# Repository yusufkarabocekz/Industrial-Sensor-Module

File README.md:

# Industrial Sensor Module

## Overview
This industrial sensor module is designed for factory automation applications, providing real-time environmental monitoring of temperature, humidity, and air quality (VOC). The module is built to withstand harsh industrial conditions and supports multiple communication protocols, making it a versatile solution for various automation systems.

## Features
- **Power Input:** 9-24V DC
- **Voltage Regulation:**
  - 5V and 3.3V regulators (LDO and DC-DC buck converter)
- **Sensors:**
  - SHT31 (Temperature & Humidity, I2C)
  - CCS811 (VOC and CO2, I2C)
  - External Analog Input (0-5V, read through 12-bit ADC)
- **Communication Interfaces:**
  - RS485 (Modbus RTU support)
  - UART & I2C external pins
  - ESP32C3 Mini onboard
- **PCB Specifications:**
  - **Dimensions:** 50mm x 50mm
  - **Layer Count:** 4-layer PCB for improved signal integrity and EMI resistance
  - **Terminal Blocks:** Phoenix Contact (or equivalent) screw terminals for RS485 and power input
  - **ESD Protection:** TVS diodes on input lines to ensure robustness

## PCB Design
The PCB layout is optimized to minimize the influence of airflow on sensor measurements. The module is compact, modular, and suitable for various industrial applications.

## PCB Images
### Front View
The front side of the PCB features the ESP32C3 Mini, sensor modules, and necessary components for power regulation and communication. 

### Back View
The back side of the PCB includes additional circuit traces, connectors, and protection components. 

### Angled View
This perspective provides a detailed look at the board's overall design, component placement, and the layout strategy used to optimize performance and durability.

## Getting Started
### Hardware Setup
1. Provide a **9-24V DC** power input via the terminal block.
2. Connect RS485 for Modbus RTU communication or use UART/I2C for direct interfacing.
3. Read sensor values via ESP32C3 Mini or any other microcontroller with supported interfaces.

### Firmware Development
- The ESP32C3 Mini can be programmed using **ESP-IDF** or **Arduino framework**.
- Libraries required:
  - `Wire.h` for I2C communication
  - `ModbusMaster.h` for Modbus RTU communication (if needed)
  - `Adafruit_SHT31.h` for SHT31 sensor
  - `Adafruit_CCS811.h` for CCS811 sensor

## Gerber Files & Manufacturing
- The **Gerber files** are available in the `gerber/` directory.
- Recommended PCB manufacturing specs:
  - **Layer Count:** 4
  - **Copper Thickness:** 1oz
  - **Surface Finish:** ENIG

## Contact
For any inquiries or contributions, feel free to open an issue or reach out.

---
_Designed with KiCad._ Designed by Yusuf Karabocek

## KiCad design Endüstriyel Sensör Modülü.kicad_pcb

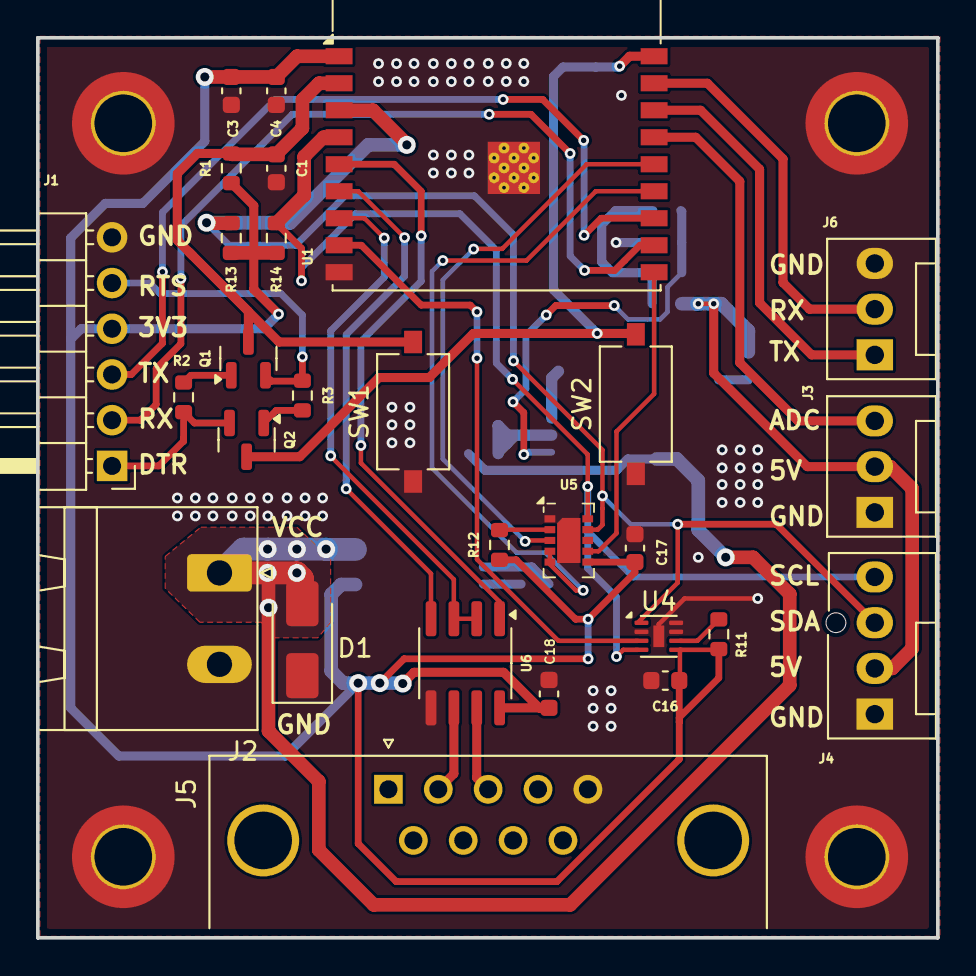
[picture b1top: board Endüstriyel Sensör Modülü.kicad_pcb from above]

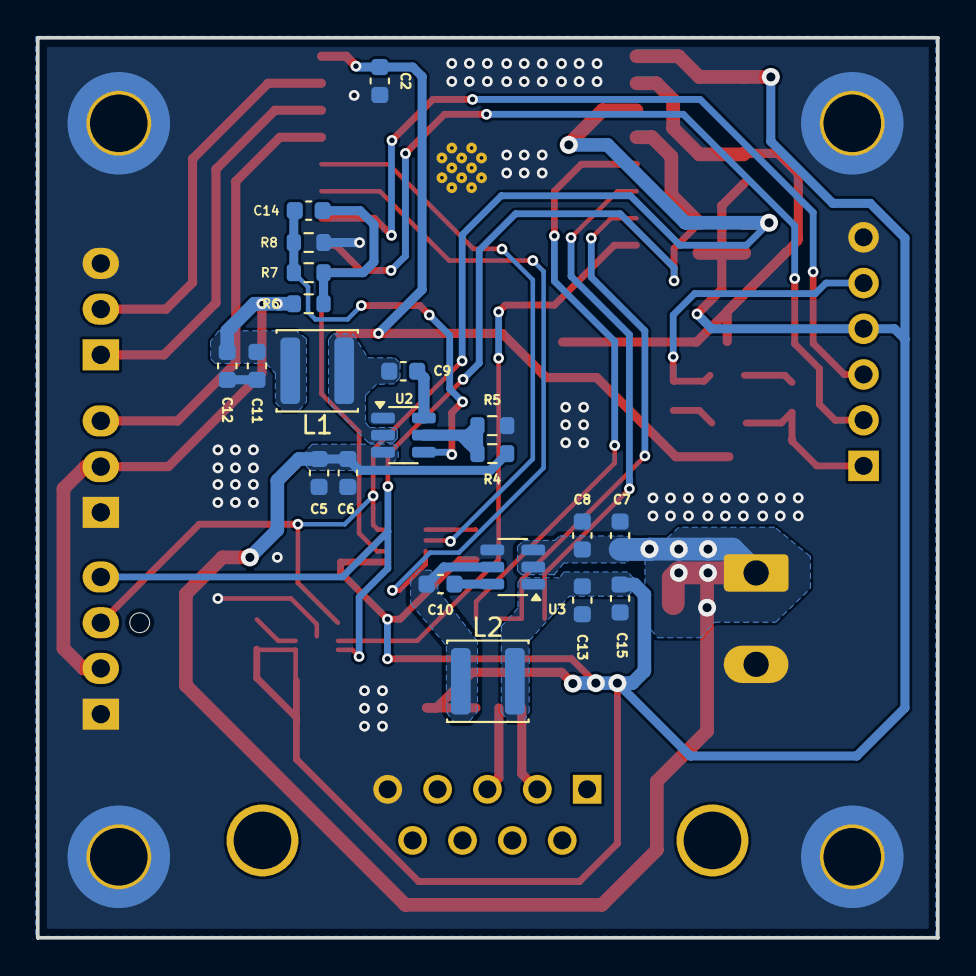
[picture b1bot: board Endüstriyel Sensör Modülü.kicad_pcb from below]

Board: 4 copper layers, 50.0 x 50.0 mm, 53 parts (21 on the bottom side), 35 nets.

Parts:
C1, C17: 1uF; C_0603_1608Metric
C2, C4, C6, C8, C9, C10, C16, C18: 100nF; C_0603_1608Metric
C3, C5, C7: 10uF; C_0603_1608Metric
C11, C12, C13, C15: 22uF; C_0603_1608Metric
C14: 75pF; C_0603_1608Metric
D1: SMAJ6.0CA; D_SMA
H1, H2, H3, H4: GND; MountingHole_3.2mm_M3_ISO7380_Pad_TopBottom
J1: FTDI232 Connector; PinHeader_1x06_P2.54mm_Horizontal
J2: POWER INPUT; PhoenixContact_MSTBA_2,5_2-G-5,08_1x02_P5.08mm_Horizontal
J3: ADC; FanPinHeader_1x03_P2.54mm_Vertical
J4: I2C; FanPinHeader_1x04_P2.54mm_Vertical
J5: DE9_Pins; DSUB-9_Pins_Horizontal_P2.77x2.84mm_EdgePinOffset4.94mm_Hou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
J6: UART; FanPinHeader_1x03_P2.54mm_Vertical
L1, L2: 10uH; L_APV_ANR4030
Q1, Q2: SS8050; SOT-23
R1: 10k; R_0603_1608Metric
R2, R3: 12k; R_0603_1608Metric
R4: 511k; R_0603_1608Metric
R5: 105k; R_0603_1608Metric
R6: 49.9k; R_0603_1608Metric
R7: 100k; R_0603_1608Metric
R8: 13.3k; R_0603_1608Metric
R11: 2k; R_0603_1608Metric
R12, R13, R14: 4.7k; R_0603_1608Metric
SW1: RESET; SW_Tactile_SPST_NO_Straight_CK_PTS636Sx25SMTRLFS
SW2: BOOT; SW_Tactile_SPST_NO_Straight_CK_PTS636Sx25SMTRLFS
U1: ESP32-C3-WROOM-02
U2: TPS54302; SOT-23-6
U3: AP63203WU; TSOT-23-6
U4: SHT31A-DIS; DFN-8-1EP_2x2mm_P0.5mm_EP0.6x1.2mm
U5: CCS811; AMS_LGA-10-1EP_2.7x4mm_P0.6mm
U6: MAX485E; SOIC-8_3.9x4.9mm_P1.27mm

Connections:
/ESP32-Microcontroller/DTR: J1.1, Q2.2 (E), R2.1
/ESP32-Microcontroller/EN: C1.1, Q1.3 (C), R1.2, SW1.2, U1.2 (EN)
/ESP32-Microcontroller/IO0: C2.1, Q2.3 (C), SW2.2, U1.18 (IO0)
/ESP32-Microcontroller/RTS: J1.5, Q1.2 (E), R3.1
/ESP32-Microcontroller/RX: J1.2, U1.11 (IO20/RXD)
/ESP32-Microcontroller/TX: J1.3, U1.12 (IO21/TXD)
ADC: J3.3, U1.15 (IO3)
ALERT: U1.8 (IO9), U4.3 (ALERT)
CCS_INT: U1.14 (IO19), U5.3 (~INT)
EXT_RX: J6.2, U1.17 (IO1)
EXT_TX: J6.1, U1.16 (IO2)
GND: C1.2, C2.2, C3.2, C4.2, C5.2, C6.2, C7.2, C8.2, C11.2, C12.2, C13.1, C15.2, C16.2, C17.2, C18.2, D1.1 (A1), H1.1, H2.1, H3.1, H4.1, J1.6, J2.2, J3.1, J4.1, J5.5, J6.3, R5.2, R8.2, SW1.1, SW2.1, U1.9 (GND), U1.19 (GND), U2.1 (GND), U3.4 (GND), U4.2 (ADDR), U4.7 (R), U4.8 (VSS), U4.9 (VSS), U5.1 (ADDR), U5.11 (GND), U6.5 (GND)
unnamed: C14.1, R6.2, R7.1
unnamed: Q1.1 (B), R2.2
unnamed: Q2.1 (B), R3.2
unnamed: C9.1, U2.6 (BOOT)
unnamed: R4.2, R5.1, U2.5 (EN)
unnamed: C14.2, R7.2, R8.1, U2.4 (FB)
unnamed: C9.2, L1.1, U2.2 (SW)
unnamed: C10.1, U3.6 (BST)
unnamed: C10.2, L2.1, U3.5 (SW)
unnamed: R11.2, U4.6 (~RESET)
unnamed: R12.2, U5.2 (~RESET)
unnamed: J5.2, U6.6 (A)
unnamed: J5.3, U6.7 (B)
PWM_CCS: U1.13 (IO18), U5.4 (PWM), U5.5 (Sense)
RS485_IO: U1.7 (IO8), U6.2 (~RE), U6.3 (DE)
RS485_RX: U1.5 (IO6), U6.1 (RO)
RS485_TX: U1.6 (IO7), U6.4 (DI)
SCL: J4.4, R14.1, U1.4 (IO5), U4.4 (SCL), U5.10 (SCL)
SDA: J4.3, R13.1, U1.3 (IO4), U4.1 (SDA), U5.9 (SDA)
VCC: C5.1, C6.1, C7.1, C8.1, D1.2 (A2), J2.1, R4.1, U2.3 (VIN), U3.2 (EN), U3.3 (IN)
VDD3V3: C3.1, C4.1, C13.2, C15.1, C16.1, C17.1, C18.1, J1.4, L2.2, R1.1, R11.1, R12.1, R13.2, R14.2, U1.1 (3V3), U3.1 (FB), U4.5 (VDD), U5.6 (VDD), U6.8 (VCC)
VDD5V: C11.1, C12.1, J3.2, J4.2, L1.2, R6.1
nWAKE: U1.10 (IO10), U5.7 (~WAKE)

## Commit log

2025-03-19 Industrial Sensor Module first update
